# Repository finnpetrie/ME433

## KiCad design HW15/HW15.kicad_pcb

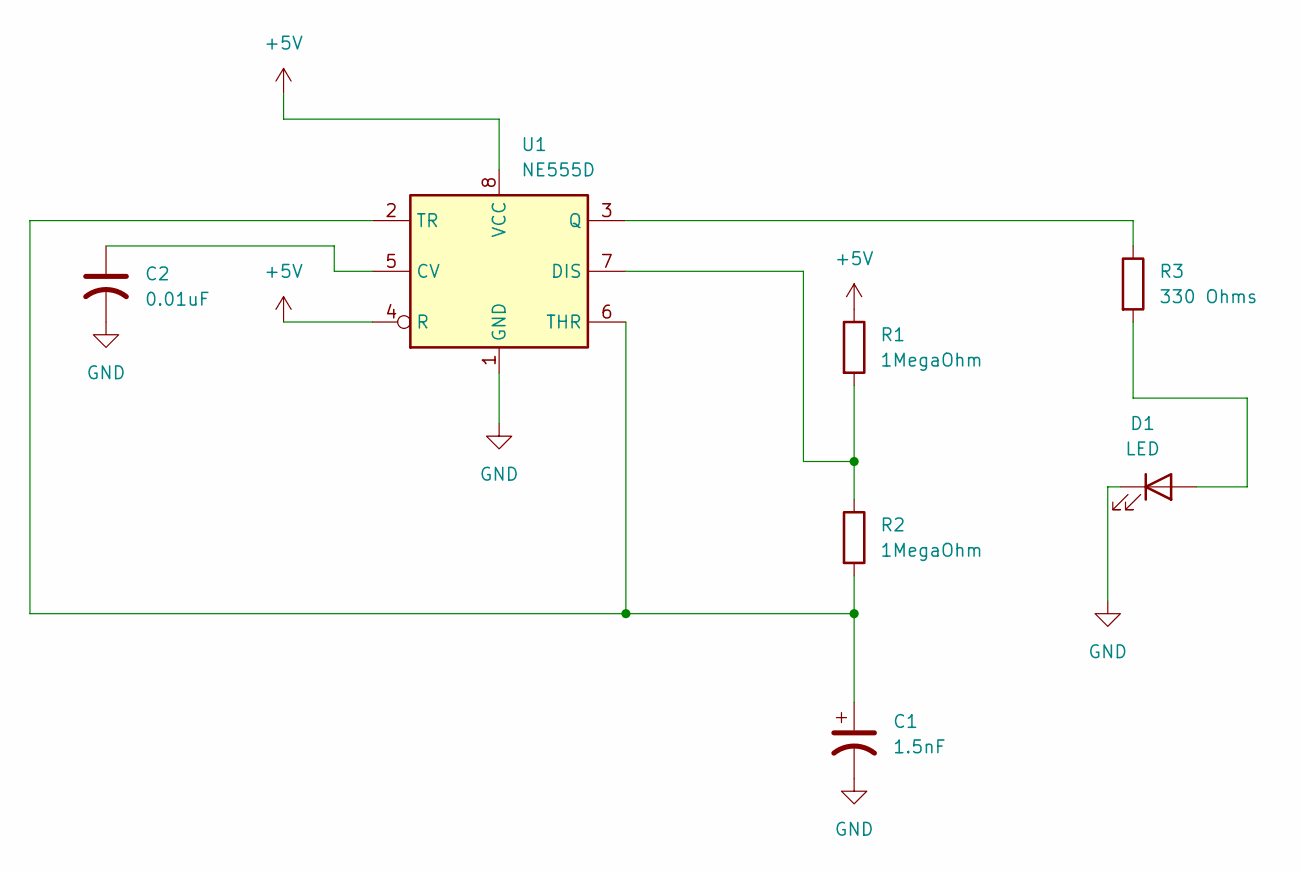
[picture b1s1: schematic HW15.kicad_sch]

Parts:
C1: 1.5nF; CP_Elec_3x5.3
C2: 0.01uF; CP_Elec_3x5.3
D1: LED; LED-APA102-2020
R1, R2: 1MegaOhm; R_0201_0603Metric
R3: 330 Ohms; R_0201_0603Metric
U1: NE555D; SOIC-8_3.9x4.9mm_P1.27mm

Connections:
+5V: R1.1, U1.4 (R), U1.8 (VCC)
GND: C1.2, C2.2, D1.1 (K), U1.1 (GND)
unnamed: D1.2 (A), R3.2
unnamed: C2.1, U1.5 (CV)
unnamed: R1.2, R2.1, U1.7 (DIS)
unnamed: R3.1, U1.3 (Q)
unnamed: C1.1, R2.2, U1.2 (TR), U1.6 (THR)

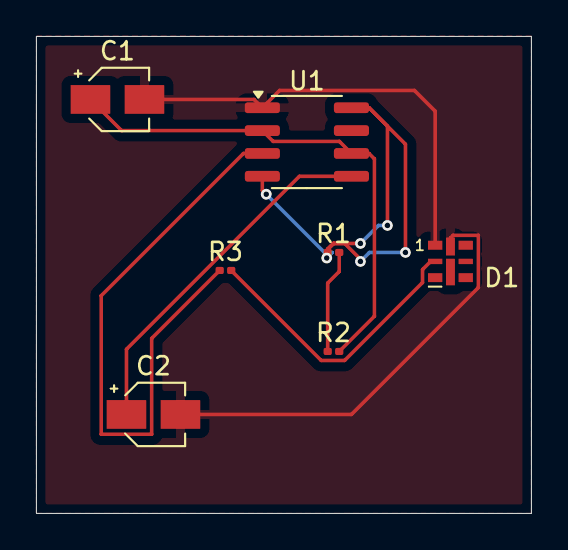
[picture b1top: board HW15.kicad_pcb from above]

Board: 2 copper layers, 27.5 x 26.5 mm, 7 parts (0 on the bottom side), 7 nets.

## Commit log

2025-05-09 Multicore HW9
2025-05-16 Mouse USB Button controller
2025-05-26 HW13
2025-06-05 HW12
2025-06-05 HW14
2025-06-05 Motors
2025-06-05 HW10
2025-06-05 HW17
2025-06-05 HW15
2025-06-05 HW18
2025-06-07 video
